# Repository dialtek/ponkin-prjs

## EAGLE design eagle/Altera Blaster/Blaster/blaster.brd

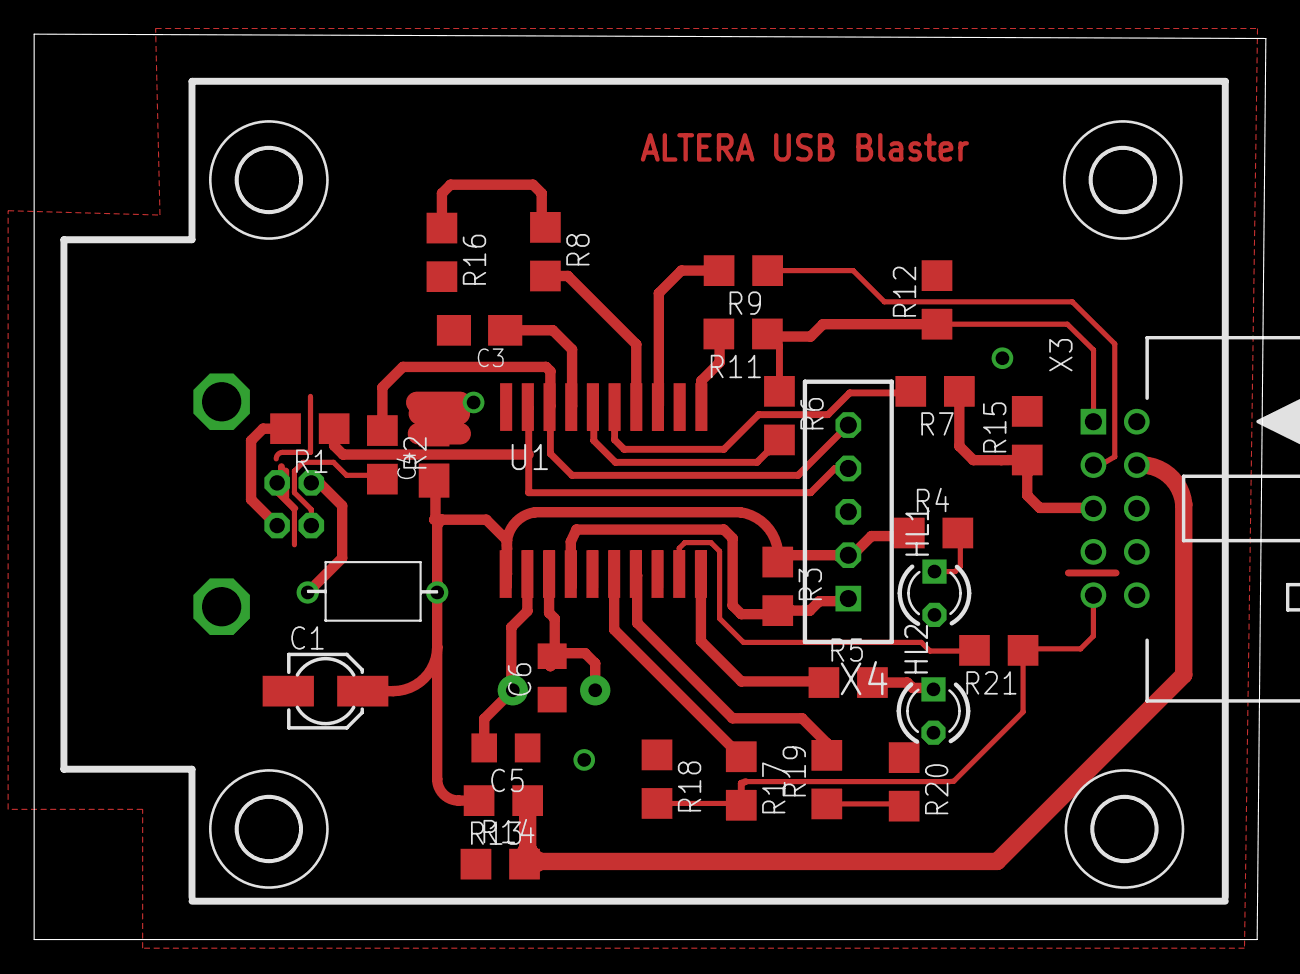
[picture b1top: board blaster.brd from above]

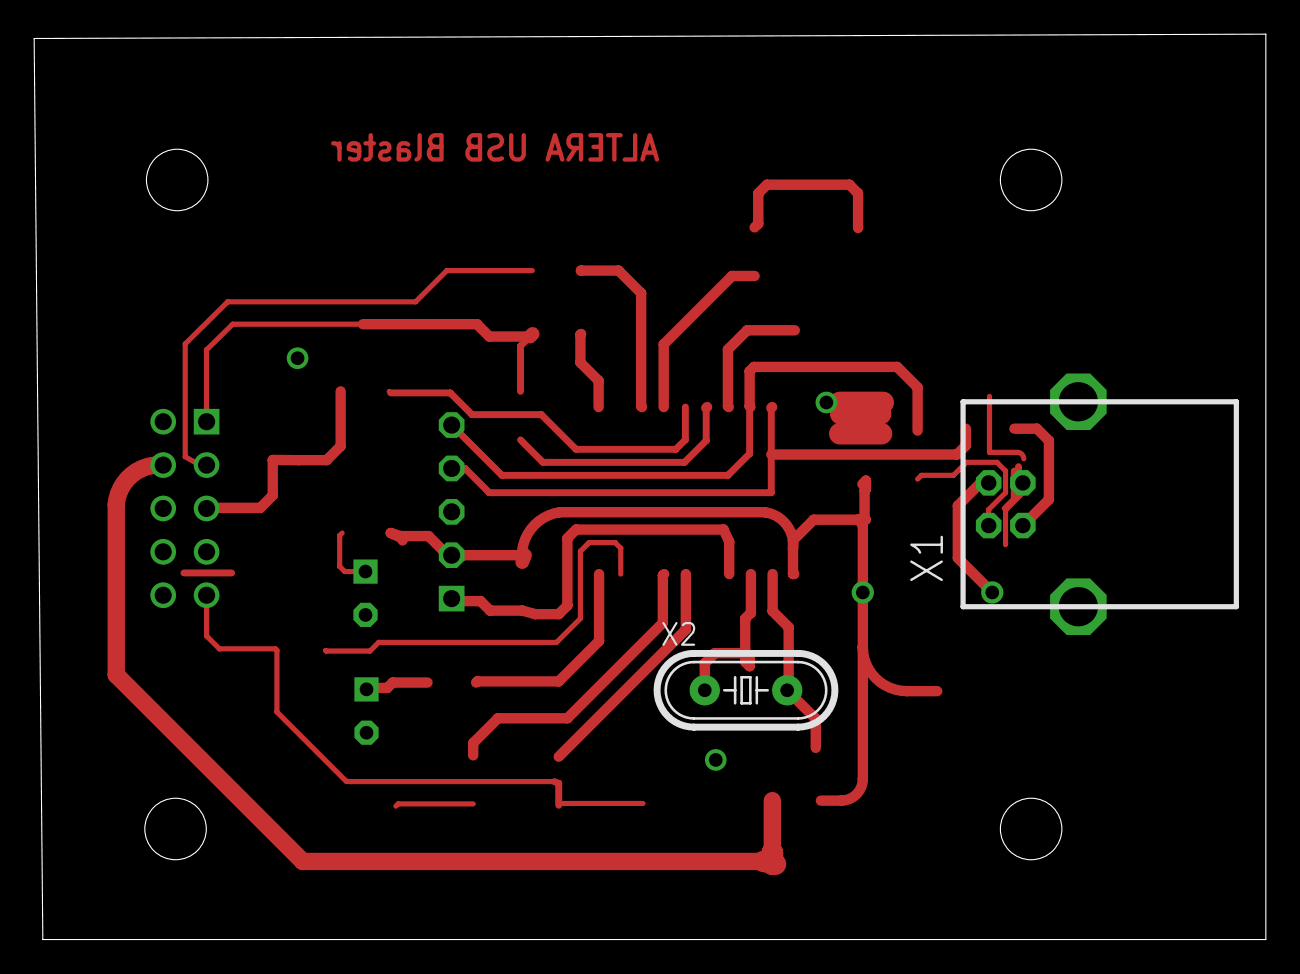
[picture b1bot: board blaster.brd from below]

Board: 2 copper layers, 72.1 x 53.0 mm, 37 parts (2 on the bottom side), 29 nets.

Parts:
C1: SMD_EL_CAP; 153CLV-0405
C3, C4: C1206K
C5, C6: 15p; C0805D
HL1, HL2: LED3MM
L1: INDUCTORIND2; INDUCTOR2
R1, R2: SMD_RES; R1206
R3: 10k; R1206
R4, R5: 1k; R1206
R6, R7, R8, R9, R11, R13, R17, R19, R21: 100; R1206
R12, R14, R15, R16, R18, R20: 200; R1206
U1: PIC18F14K50D; SO20-DW
U$1, U$2, U$3, U$4: 3,6
X1: USBB-1J
X2: 12М; HC49/S
X3: X; PAK100/2500-5-10
X4: PIC_ISP_CONN; PLC-5PIN

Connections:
+5V: C1.+, C4.1, L1.P$1, R3.1, R4.1, R13.2, U1.1.1, X4.P$2
GND: C1.-, C3.2, C4.2, C5.1, C6.1, HL1.K, HL2.K, R12.2, R14.1, R15.2, R16.2, R18.1, R20.1, U1.1.20, X1.4, X1.5, X1.6, X3.2, X3.10, X4.P$3
MCLR: R3.2, U1.1.4, X4.P$1
unnamed: R1.2, X1.3
unnamed: L1.P$2, X1.1
unnamed: R2.2, X1.2
unnamed: C3.1, U1.1.17
unnamed: HL1.A, R4.2
unnamed: R5.1, U1.1.10
unnamed: C5.2, U1.1.2, X2.2
unnamed: C6.2, U1.1.3, X2.1
unnamed: HL2.A, R5.2
unnamed: R6.2, U1.1.16
unnamed: R17.1, U1.1.6
unnamed: R7.2, U1.1.15
unnamed: R8.2, U1.1.14
unnamed: R9.2, U1.1.13
unnamed: R11.2, U1.1.11
unnamed: R19.2, U1.1.7
unnamed: R21.2, U1.1.9
NCE: R8.1, R16.1
NCS: R19.1, R20.2
PGC: R2.1, U1.1.18, X4.P$5
PGD: R1.1, U1.1.19, X4.P$4
TCK: R6.1, R11.1, R12.1, X3.1
TDI: R17.2, R18.2, R21.1, X3.9
TDO: R9.1, X3.3
TMS: R7.1, R15.1, X3.5
VCC_3.3: R13.1, R14.2, X3.4

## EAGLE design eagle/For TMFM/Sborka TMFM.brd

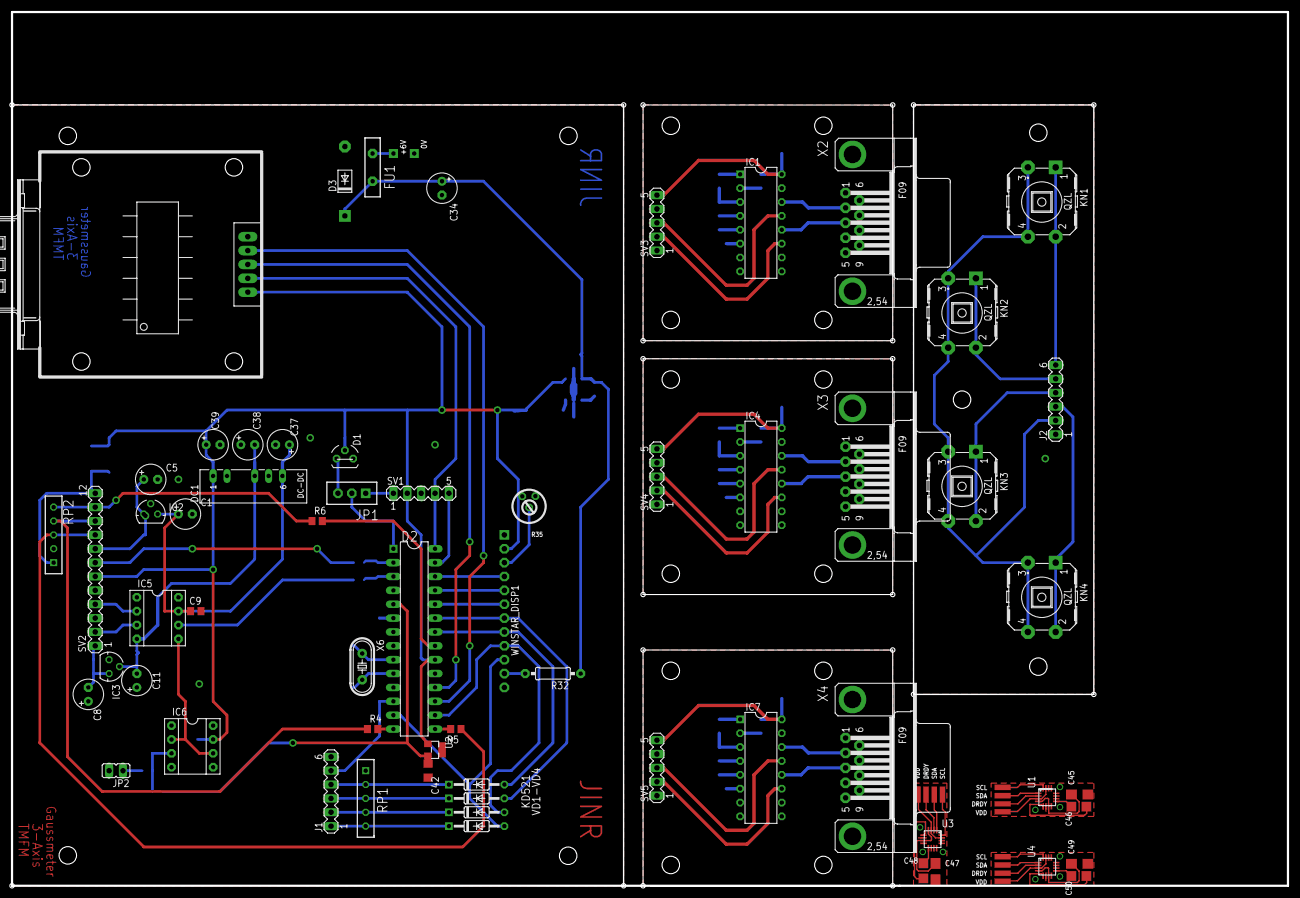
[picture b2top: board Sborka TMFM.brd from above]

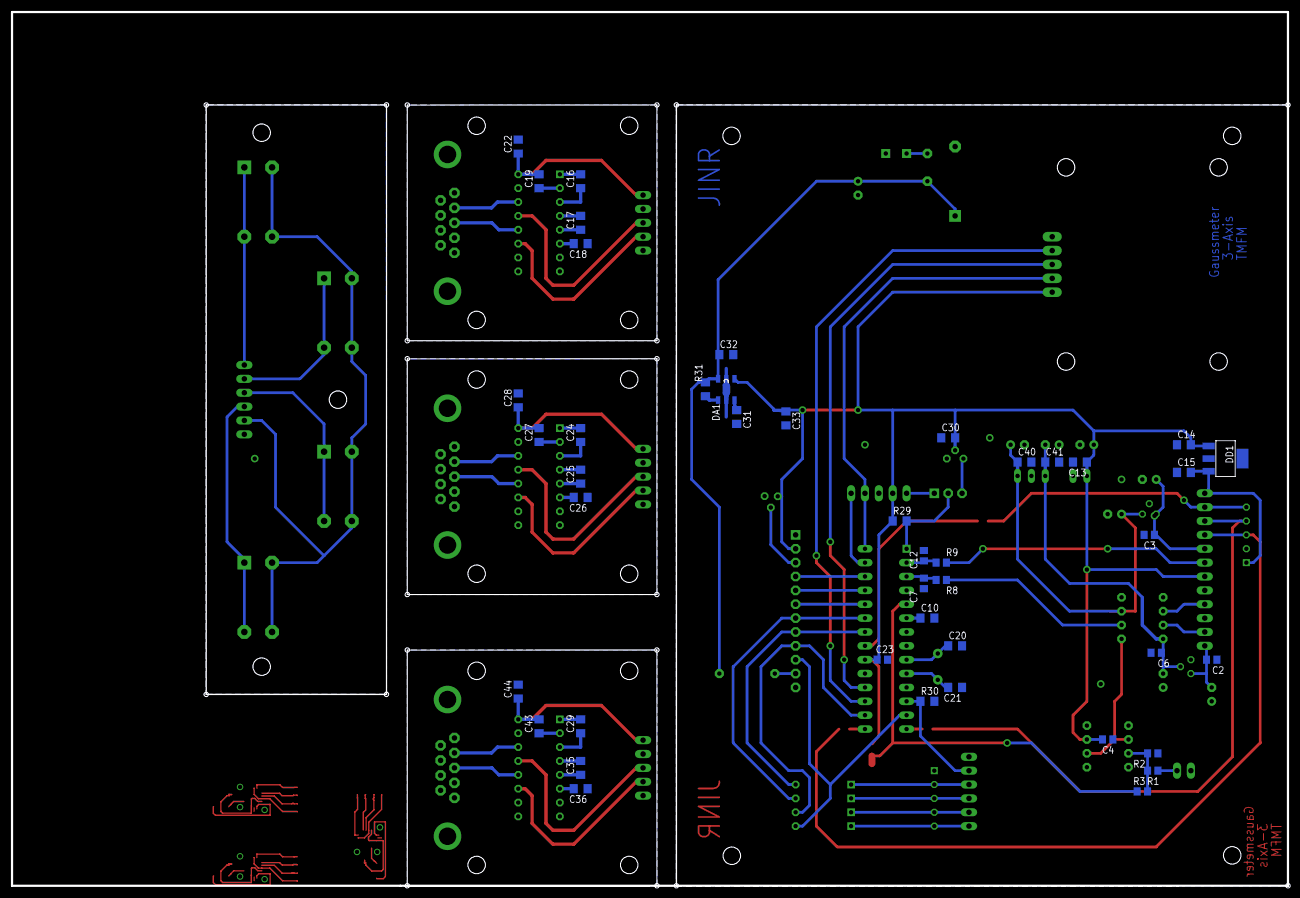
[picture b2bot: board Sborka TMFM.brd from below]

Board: 2 copper layers, 233.7 x 160.0 mm, 120 parts (44 on the bottom side), 116 nets.

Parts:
0V: PIN1
+6V: PIN1
C1, C5, C8, C11: 100 uF; E2,5-6
C2, C3, C12, C23: 0.1; C0805
C4, C6, C7, C9: 0,1; C0805
C10, C14, C30, C40, C41: 0.1; C0805D
C13: 100n; C0805D
C15: 10uF; C0805D
C16, C17, C18, C19, C22, C24, C25, C26, C27, C28, C29, C32, C35, C36, C43, C44: C0805D
C20, C21: 16p; C0805D
C31: 10n; C0805D
C33, C42: 1uF; C0805D
C34: 100uFx25v; E2,5-6
C37, C38, C39: 100uFx25V; E2,5-6
C45, C47, C49: 4.7; C1206K
C46, C48, C50: 0.22; C0805K
D1: DS1811; TO92-60
D2: PIC18F25k80DIP; DIL28-3
D3: 1N5061; DO41-10
DA1: NJM2880; SOT89-5
DC1: NMA@1
DD1: LM2937; SOT223
FU1: RA90
IC1, IC4, IC7: MAX232; DIL16
IC2: 78L05; 78LXX
IC3: 79L05; 79LXX
IC5: INA128P; DIL08@1
IC6: OPA340P; DIL08@1
J1: MA06-1@1
J2: MA06-1
JP1: JP3PIN; PLC-3PIN
JP2: JP1@1
KN1, KN2, KN3, KN4: LZQ-KN
P1, P6, P10: SDA; 1_PIN_PLANAR
P2, P4, P9: VDD 3.3; 1_PIN_PLANAR
P3, P7, P11: SCL; 1_PIN_PLANAR
P5, P8, P12: DRDY; 1_PIN_PLANAR
R1, R2, R3: R0805
R4, R5, R6: 330; R0805
R8, R9: 1k; R0805
R29, R30: 10k; R0805D
R31: 10K; R0805D
R32: 0207/10
R35: 15K; RTRIM3329H
RP1: SIP5
RP2: 10k; SIP5
SV1: MA05-1@1
SV2: MA12-1
SV3, SV4, SV5: MA05-1
U1, U3, U4: HMC5883; QFN16-4X4
U2: REF3140; SOT23-W
VD1, VD2, VD3, VD4: KD521; DO35-10
WINSTAR_DISP1: WINSTAR16X4_12
X1: KM_RS_232
X2, X3, X4: F09HP
X6: 10 MHz; HC49/S

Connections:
0V: 0V.P$1, C1.-, C2.2, C3.2, C4.1, C5.-, C6.2, C7.2, C8.+, C9.2, C10.2, C11.+, C12.2, C13.2, C14.1, C15.1, C20.2, C21.1, C23.2, C30.1, C31.2, C32.2, C33.2, C34.-, C37.-, C38.+, C39.-, C40.2, C41.2, C42.1, D1.3, D2.8, D2.19, D3.A, DA1.2, DA1.21, DC1.2, DC1.5, DD1.GND, DD1.GND@1, IC2.GND, IC3.GND, IC6.4, J1.6, JP2.2, R2.1, R30.P$2, R35.1, RP1.1, SV1.3, SV2.3, SV2.5, U2.GND, WINSTAR_DISP1.P$1, WINSTAR_DISP1.P$12, X1.1
0V1: C18.1, C22.2, IC1.8, IC1.10, IC1.15, SV3.1, X2.5, X2.G1, X2.G2
0V2: C26.1, C28.2, IC4.8, IC4.10, IC4.15, SV4.1, X3.5, X3.G1, X3.G2
0V3: C36.1, C44.2, IC7.8, IC7.10, IC7.15, SV5.1, X4.5, X4.G1, X4.G2
0V4: C45.2, U1.P$9, U1.P$11
0V5: C47.2, U3.P$9, U3.P$11
0V6: C49.2, U4.P$9, U4.P$11
+3V3: C15.2, DD1.OUTPUT, RP2.1, SV2.12
+5V: C4.2, C13.1, C14.2, C23.1, C30.2, C33.1, C39.+, D1.2, D2.20, DA1.4, DC1.1, DD1.INPUT, IC6.7, R29.P$1, R35.2, SV1.2, SV2.6, U2.IN, WINSTAR_DISP1.P$2, X1.5
+5V1: C19.2, C22.1, IC1.16, SV3.5
+5V2: C27.2, C28.1, IC4.16, SV4.5
+5V3: C43.2, C44.1, IC7.16, SV5.5
+5V4: J2.2, KN1.3, KN1.4, KN2.3, KN2.4, KN3.3, KN3.4, KN4.3, KN4.4
+6V: C32.1, C34.+, D3.C, DA1.5, FU1.P$2, R31.P$2, R32.1
+15V: C1.+, C9.1, C37.+, C40.1, DC1.6, IC2.IN, IC5.7
-15V: C6.1, C11.-, C38.-, C41.1, DC1.4, IC3.IN, IC5.4
AN0: C12.1, D2.2, R9.2
AN1: C7.1, D2.3, R8.2
MCLR: JP1.P$1, SV1.1
unnamed: J1.2, RP1.4, VD3.C
unnamed: C20.1, D2.9, X6.1
unnamed: J1.3, RP1.3, VD2.C
unnamed: C21.2, D2.10, X6.2
unnamed: J1.4, RP1.2, VD1.C
unnamed: C16.2, IC1.1
unnamed: D2.1, JP1.P$2, R29.P$2
unnamed: J1.1, RP1.5, VD4.C
unnamed: C16.1, IC1.3
unnamed: C17.2, IC1.4
unnamed: C2.1, C8.-, IC3.OUT, SV2.1
unnamed: IC5.2, SV2.4
unnamed: IC5.3, SV2.2
unnamed: IC5.5, IC6.2, IC6.6
unnamed: IC6.3, R1.1, R2.2, R3.2
unnamed: JP2.1, R3.1
unnamed: IC5.6, R8.1
unnamed: R4.1, RP2.4, SV2.10
unnamed: R32.2, WINSTAR_DISP1.P$11
unnamed: R5.1, RP2.3, SV2.9
unnamed: +6V.P$1, FU1.P$1
unnamed: C17.1, IC1.5
unnamed: D1.1, JP1.P$3
unnamed: R35.3, WINSTAR_DISP1.P$3
unnamed: C10.1, D2.6
unnamed: C18.2, IC1.6
unnamed: IC1.14, X2.2
unnamed: C3.1, C5.+, IC2.OUT, SV2.8
unnamed: R9.1, SV2.7
unnamed: R6.1, RP2.5, SV2.11
unnamed: IC1.12, X2.3
unnamed: C19.1, IC1.2
unnamed: C24.2, IC4.1
unnamed: C24.1, IC4.3
unnamed: C25.2, IC4.4
unnamed: C25.1, IC4.5
unnamed: C26.2, IC4.6
unnamed: IC4.14, X3.2
unnamed: IC4.12, X3.3
unnamed: C27.1, IC4.2
unnamed: C29.2, IC7.1
unnamed: C29.1, IC7.3
unnamed: C35.2, IC7.4
unnamed: C35.1, IC7.5
unnamed: C36.2, IC7.6
unnamed: IC7.14, X4.2
unnamed: IC7.12, X4.3
unnamed: DA1.1, R31.P$1
unnamed: C31.1, DA1.3
unnamed: C43.1, IC7.2
unnamed: J2.6, KN1.1, KN1.2
unnamed: J2.5, KN2.1, KN2.2
unnamed: J2.4, KN3.1, KN3.2
unnamed: J2.3, KN4.1, KN4.2
unnamed: C45.1, U1.P$10, U1.P$13
unnamed: C46.1, U1.P$8
unnamed: C46.2, U1.P$12
unnamed: P2.P$1, U1.P$2, U1.P$14
unnamed: P3.P$1, U1.P$1
unnamed: P1.P$1, U1.P$16
unnamed: P5.P$1, U1.P$15
unnamed: C47.1, U3.P$10, U3.P$13
unnamed: C48.1, U3.P$8
unnamed: C48.2, U3.P$12
unnamed: P4.P$1, U3.P$2, U3.P$14
unnamed: P7.P$1, U3.P$1
unnamed: P6.P$1, U3.P$16
unnamed: P8.P$1, U3.P$15
unnamed: C49.1, U4.P$10, U4.P$13
unnamed: C50.1, U4.P$8
unnamed: C50.2, U4.P$12
unnamed: P9.P$1, U4.P$2, U4.P$14
unnamed: P11.P$1, U4.P$1
unnamed: P10.P$1, U4.P$16
unnamed: P12.P$1, U4.P$15
PGC: D2.27, SV1.5
PGD: D2.28, SV1.4, X1.4
RB0: D2.21, R6.2
RB1: D2.22, VD1.A, WINSTAR_DISP1.P$8
RB2: D2.23, VD2.A, WINSTAR_DISP1.P$7
RB3: D2.24, WINSTAR_DISP1.P$6
RB4: D2.25, WINSTAR_DISP1.P$5
RB5: D2.26, WINSTAR_DISP1.P$4
RC1: D2.12, J1.5, R30.P$1
RC2: D2.13, VD4.A, WINSTAR_DISP1.P$10
RC3: D2.14, R4.2
RC4: D2.15, R5.2
RC5: D2.16, VD3.A, WINSTAR_DISP1.P$9
REF: C42.2, D2.5, R1.2, U2.OUT
RX: D2.18, X1.3
RX1: IC1.13, SV3.3
RX2: IC4.13, SV4.3
RX3: IC7.13, SV5.3
TX: D2.17, X1.2
TX1: IC1.11, SV3.2
TX2: IC4.11, SV4.2
TX3: IC7.11, SV5.2

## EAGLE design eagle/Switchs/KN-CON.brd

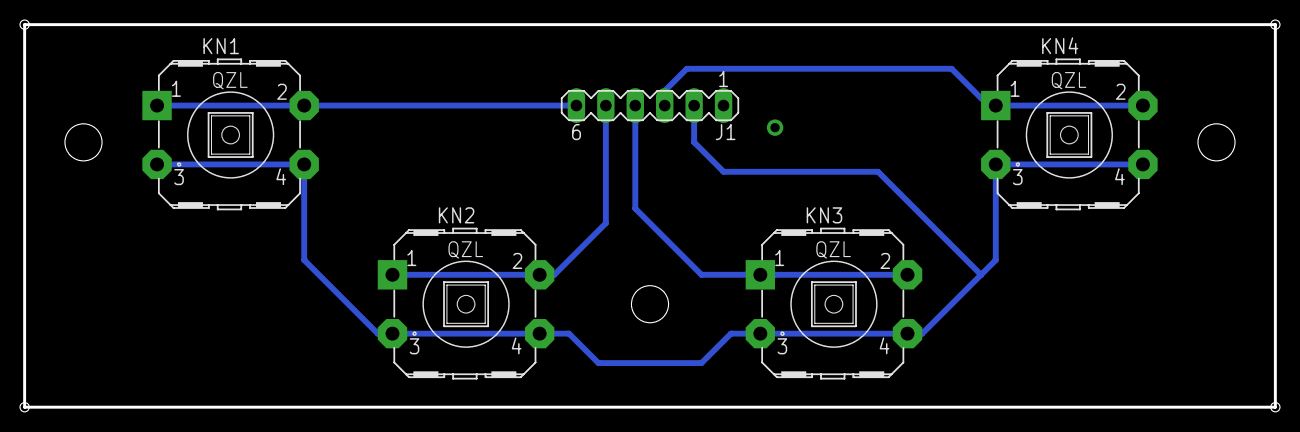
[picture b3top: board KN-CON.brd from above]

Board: 2 copper layers, 108.0 x 33.0 mm, 5 parts (0 on the bottom side), 5 nets.

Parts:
J1: MA06-1
KN1, KN2, KN3, KN4: LZQ-KN

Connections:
+5V: J1.2, KN1.3, KN1.4, KN2.3, KN2.4, KN3.3, KN3.4, KN4.3, KN4.4
unnamed: J1.6, KN1.1, KN1.2
unnamed: J1.5, KN2.1, KN2.2
unnamed: J1.4, KN3.1, KN3.2
unnamed: J1.3, KN4.1, KN4.2

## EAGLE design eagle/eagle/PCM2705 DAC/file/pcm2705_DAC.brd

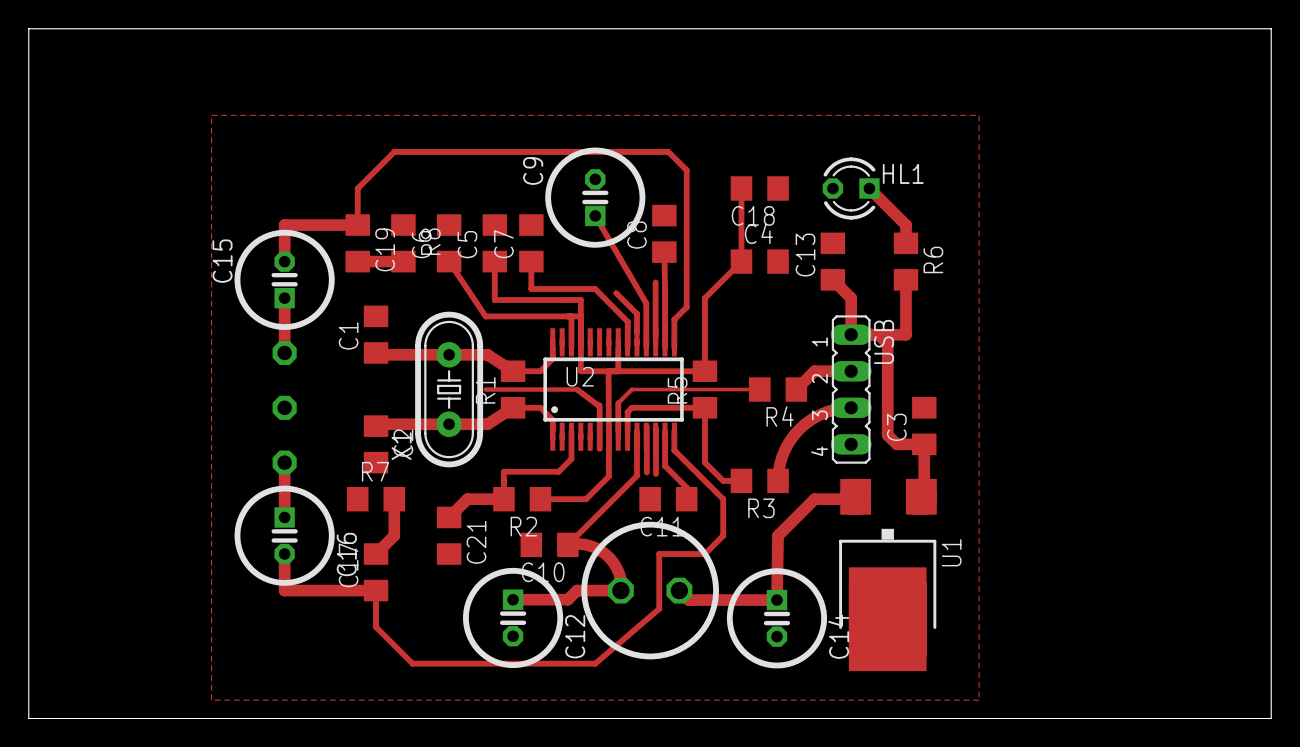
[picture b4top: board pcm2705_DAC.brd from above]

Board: 2 copper layers, 86.3 x 47.9 mm, 37 parts (0 on the bottom side), 23 nets.

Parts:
C1, C2: 33p; C0805D
C3, C4, C5, C6, C10, C13, C18, C21: 0.1u; C0805D
C7, C8, C11: 1u; C0805D
C9, C12: 10u; C100MILX6X12
C14: 2.2u; C100MILX6X12
C15, C16: 100u; C100MILX6X12
C17, C19: 22n; C0805D
HL1: LED3MM
L1: INDUCTOR
P1, P2, P3: 1_PIN_CON
R1: 1M; R0805D
R2, R5, R7, R8: 1k5; R0805D
R3, R4: 22R; R0805D
R6: 1k; R0805D
U1: LF33; LF33_DPAK
U2: PCM2705; PCM2705-TSSOP28
USB: JP4
X1: 12; HC49/S

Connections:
0V: C1.2, C2.2, C3.2, C4.2, C5.2, C6.2, C7.2, C8.2, C9.MINUS, C10.2, C11.2, C12.MINUS, C13.2, C14.MINUS, C18.1, C21.2, HL1.K, P3.P$1, R7.P$1, R8.P$1, U1.@GND1, U2.6, U2.11, U2.12, U2.17, U2.19, USB.4
+3.3V: C10.1, C12.PLUS, L1.P$2, U2.10
+5V: C3.1, C13.1, R6.P$2, U1.@IN1, USB.1
unnamed: C2.1, R1.P$1, U2.1, X1.1
unnamed: C7.1, U2.20
unnamed: C1.1, R1.P$2, U2.28, X1.2
unnamed: C21.1, R2.P$2, U2.3
unnamed: R3.P$2, R5.P$1, U2.9
unnamed: R4.P$2, U2.8
unnamed: R3.P$1, USB.3
unnamed: R4.P$1, USB.2
unnamed: HL1.A, R6.P$1
unnamed: C8.1, U2.16
unnamed: C9.PLUS, U2.18
unnamed: C15.PLUS, P1.P$1
unnamed: C11.1, U2.13
unnamed: C16.PLUS, P2.P$1
unnamed: C14.PLUS, L1.P$1, U1.@OUT1
unnamed: C16.MINUS, C17.1, U2.14
unnamed: C17.2, R7.P$2
unnamed: C15.MINUS, C19.1, U2.15
unnamed: C19.2, R8.P$2
VDD: C4.1, C5.1, C6.1, C18.2, R2.P$1, R5.P$2, U2.7, U2.21, U2.25, U2.26

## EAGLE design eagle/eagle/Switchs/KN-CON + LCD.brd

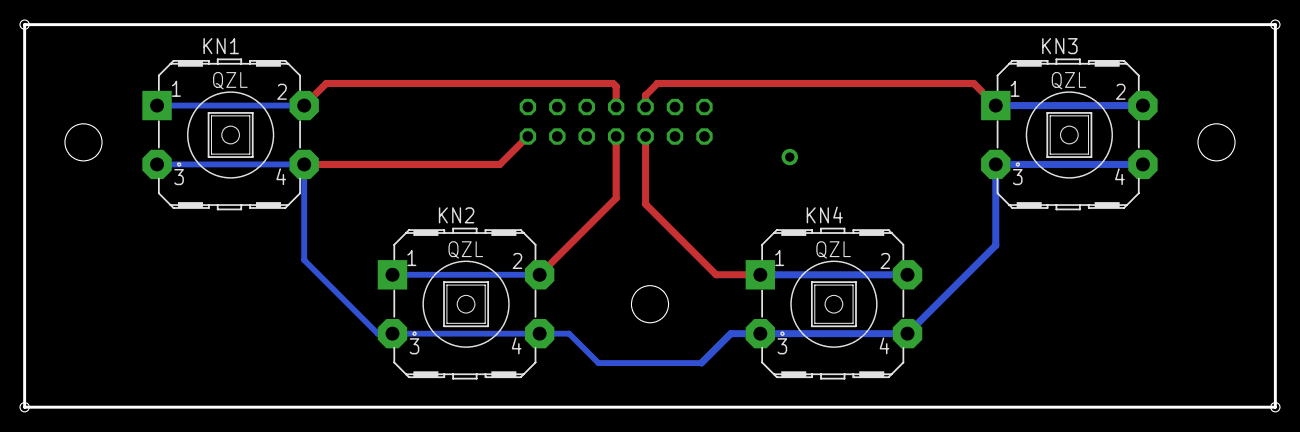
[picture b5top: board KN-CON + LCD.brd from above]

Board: 2 copper layers, 108.0 x 33.0 mm, 5 parts (1 on the bottom side), 5 nets.

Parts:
KN1, KN2, KN3, KN4: LZQ-KN
SV1: ML14

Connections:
+5V: KN1.3, KN1.4, KN2.3, KN2.4, KN3.3, KN3.4, KN4.3, KN4.4, SV1.2
LCD_DB4: KN1.1, KN1.2, SV1.7
LCD_DB5: KN2.1, KN2.2, SV1.8
LCD_DB6: KN3.1, KN3.2, SV1.9
LCD_DB7: KN4.1, KN4.2, SV1.10
